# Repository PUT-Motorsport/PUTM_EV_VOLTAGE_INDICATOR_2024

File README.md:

# Voltage Indicator 2024
The Voltage Indicator is based on a [STEVAL-VP26K01B](https://www.st.com/en/evaluation-tools/steval-vp26k01b.html) board which has a wide range input of up to ~870V DC and needs a minumum voltage of 60 V DC to operate making it a good fit for the voltage indicator.

# Stuff
https://www.4qdtec.com/csm.html

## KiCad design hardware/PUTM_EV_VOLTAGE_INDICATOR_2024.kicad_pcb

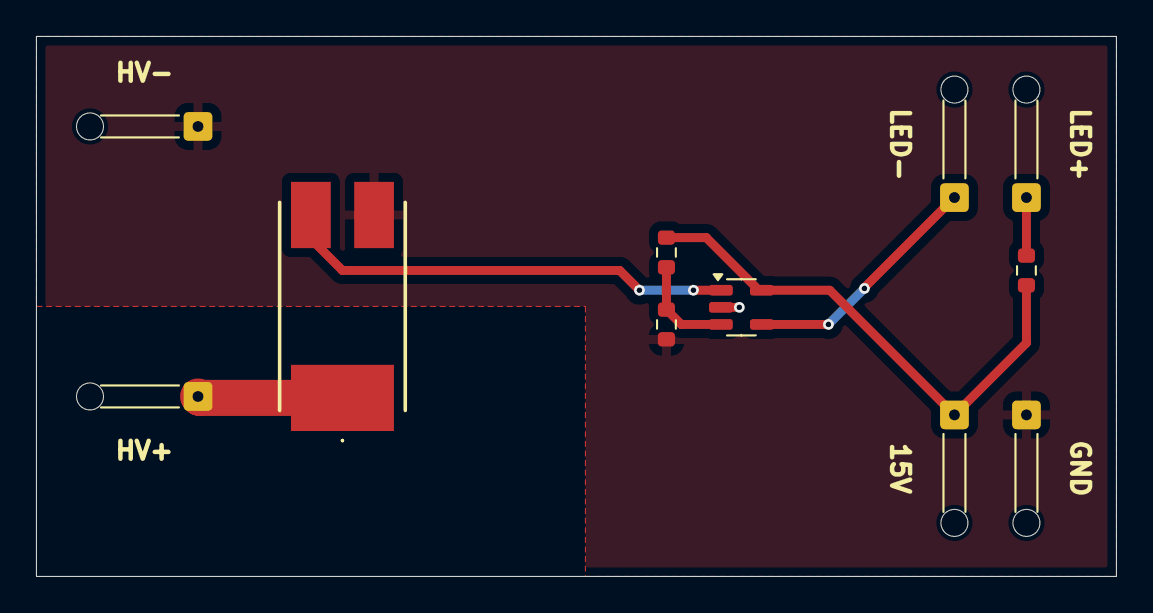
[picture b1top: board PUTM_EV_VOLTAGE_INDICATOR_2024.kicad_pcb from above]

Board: 2 copper layers, 60.0 x 30.0 mm, 11 parts (0 on the bottom side), 7 nets.

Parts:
J11, J12, J15, J16, J17, J20: PCB_PAD; SolderWire-0.1sqmm_1x01_D0.4mm_OD1mm_Relief
R1, R3: 1k; R_0603_1608Metric
R2: 67k; R_0603_1608Metric
RD1: CDMM20M0F2500DET
U2: LM397; SOT-23-5

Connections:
/15V+: J15.1, R1.1, R2.1, U2.5
/GND: J12.1, J16.1, R3.2, RD1.2, U2.2
/HV+: J11.1, RD1.1
/HV_MES: RD1.3, U2.1
/LED_POW: J17.1, R1.2
/LED_SINK: J20.1, U2.4
/REF: R2.2, R3.1, U2.3

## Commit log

2024-03-15 VI schematic & doc
2024-03-18 plan b using a diac relaxation oscilator
2024-03-26 schematic updated
2024-03-26 esf changes
2024-04-09 esf documantation update
2024-04-14 esf correction
2024-05-27 pcb done
2024-05-27 schematic errors fix
2025-04-30 comparator fix
